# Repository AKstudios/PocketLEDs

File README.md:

# PocketLEDs

Just a small board that fades 3 LEDs running on a coin-cell battery.

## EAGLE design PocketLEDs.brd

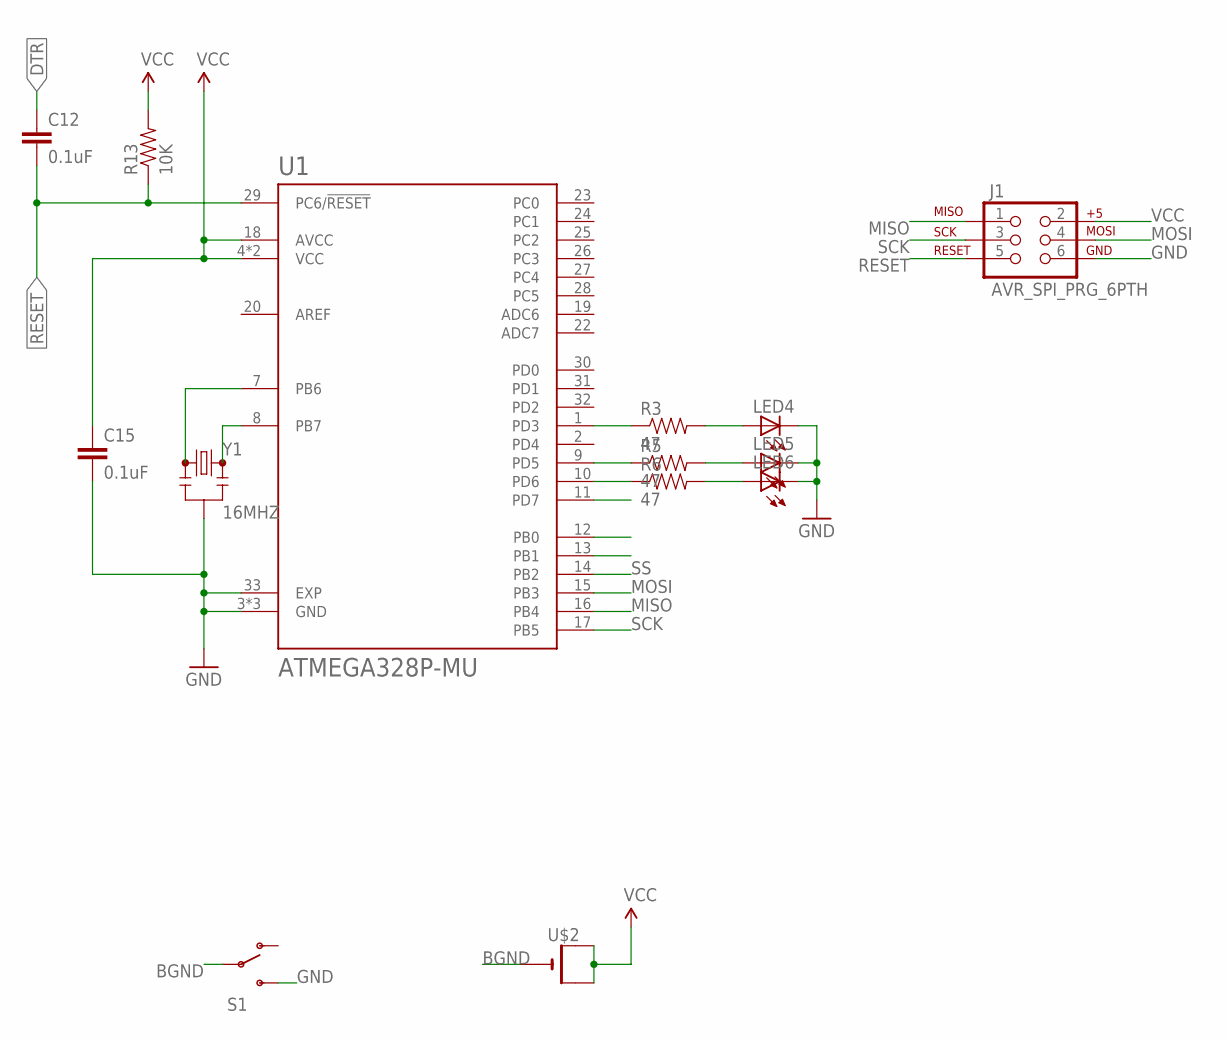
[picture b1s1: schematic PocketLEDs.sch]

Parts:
C12, C15: 0.1uF; 0805
J1: AVR_SPI_PRG_6PTH; 2X3
LED4, LED5, LED6: LEDCHIPLED_0805; CHIPLED_0805
R3, R5, R6: 47; 0805
R13: 10K; 0805
S1: SWITCH-SPDT-SMD-A; SWITCH-SPST-SMD-A
U1: ATMEGA328P-MU; QFN50P500X500X100-33N
U$2: CR2032THM; CR2032-THRU
Y1: 16MHZ; RESONATOR-SMD

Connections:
BGND: S1.2, U$2.-
DTR: C12.1
GND: C15.2, J1.6, LED4.C, LED5.C, LED6.C, S1.3 (S), U1.3 (GND), U1.5 (GND), U1.21 (GND), U1.33 (EXP), Y1.2
MISO: J1.1, U1.16 (PB4)
MOSI: J1.4, U1.15 (PB3)
unnamed: R3.1, U1.1 (PD3)
unnamed: LED4.A, R3.2
unnamed: R5.1, U1.9 (PD5)
unnamed: LED5.A, R5.2
unnamed: U1.8 (PB7), Y1.3
unnamed: U1.7 (PB6), Y1.1
unnamed: R6.1, U1.10 (PD6)
unnamed: LED6.A, R6.2
RESET: C12.2, J1.5, R13.1, U1.29 (PC6/!RESET)
SCK: J1.3, U1.17 (PB5)
SS: U1.14 (PB2)
VCC: C15.1, J1.2, R13.2, U1.4 (VCC), U1.6 (VCC), U1.18 (AVCC), U$2.+1 (+), U$2.+2 (+1)

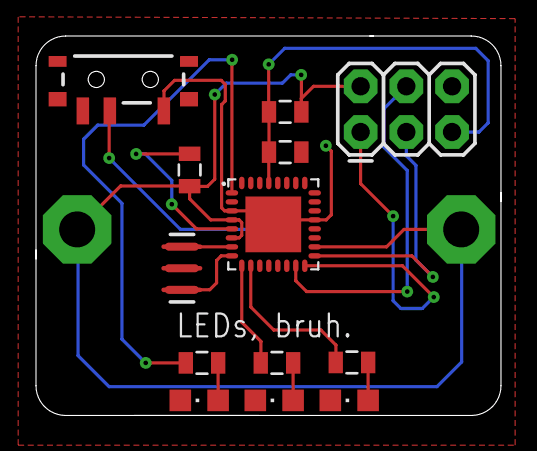
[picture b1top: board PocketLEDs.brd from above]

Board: 2 copper layers, 25.8 x 21.1 mm, 14 parts (1 on the bottom side), 15 nets.

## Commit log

2016-12-05 Fixed GND traces

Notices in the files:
parts and their libraries:
SparkFun-Resistors: Licensing: Creative Commons ShareAlike 4.0 International - https://creativecommons.org/licenses/by-sa/4.0
